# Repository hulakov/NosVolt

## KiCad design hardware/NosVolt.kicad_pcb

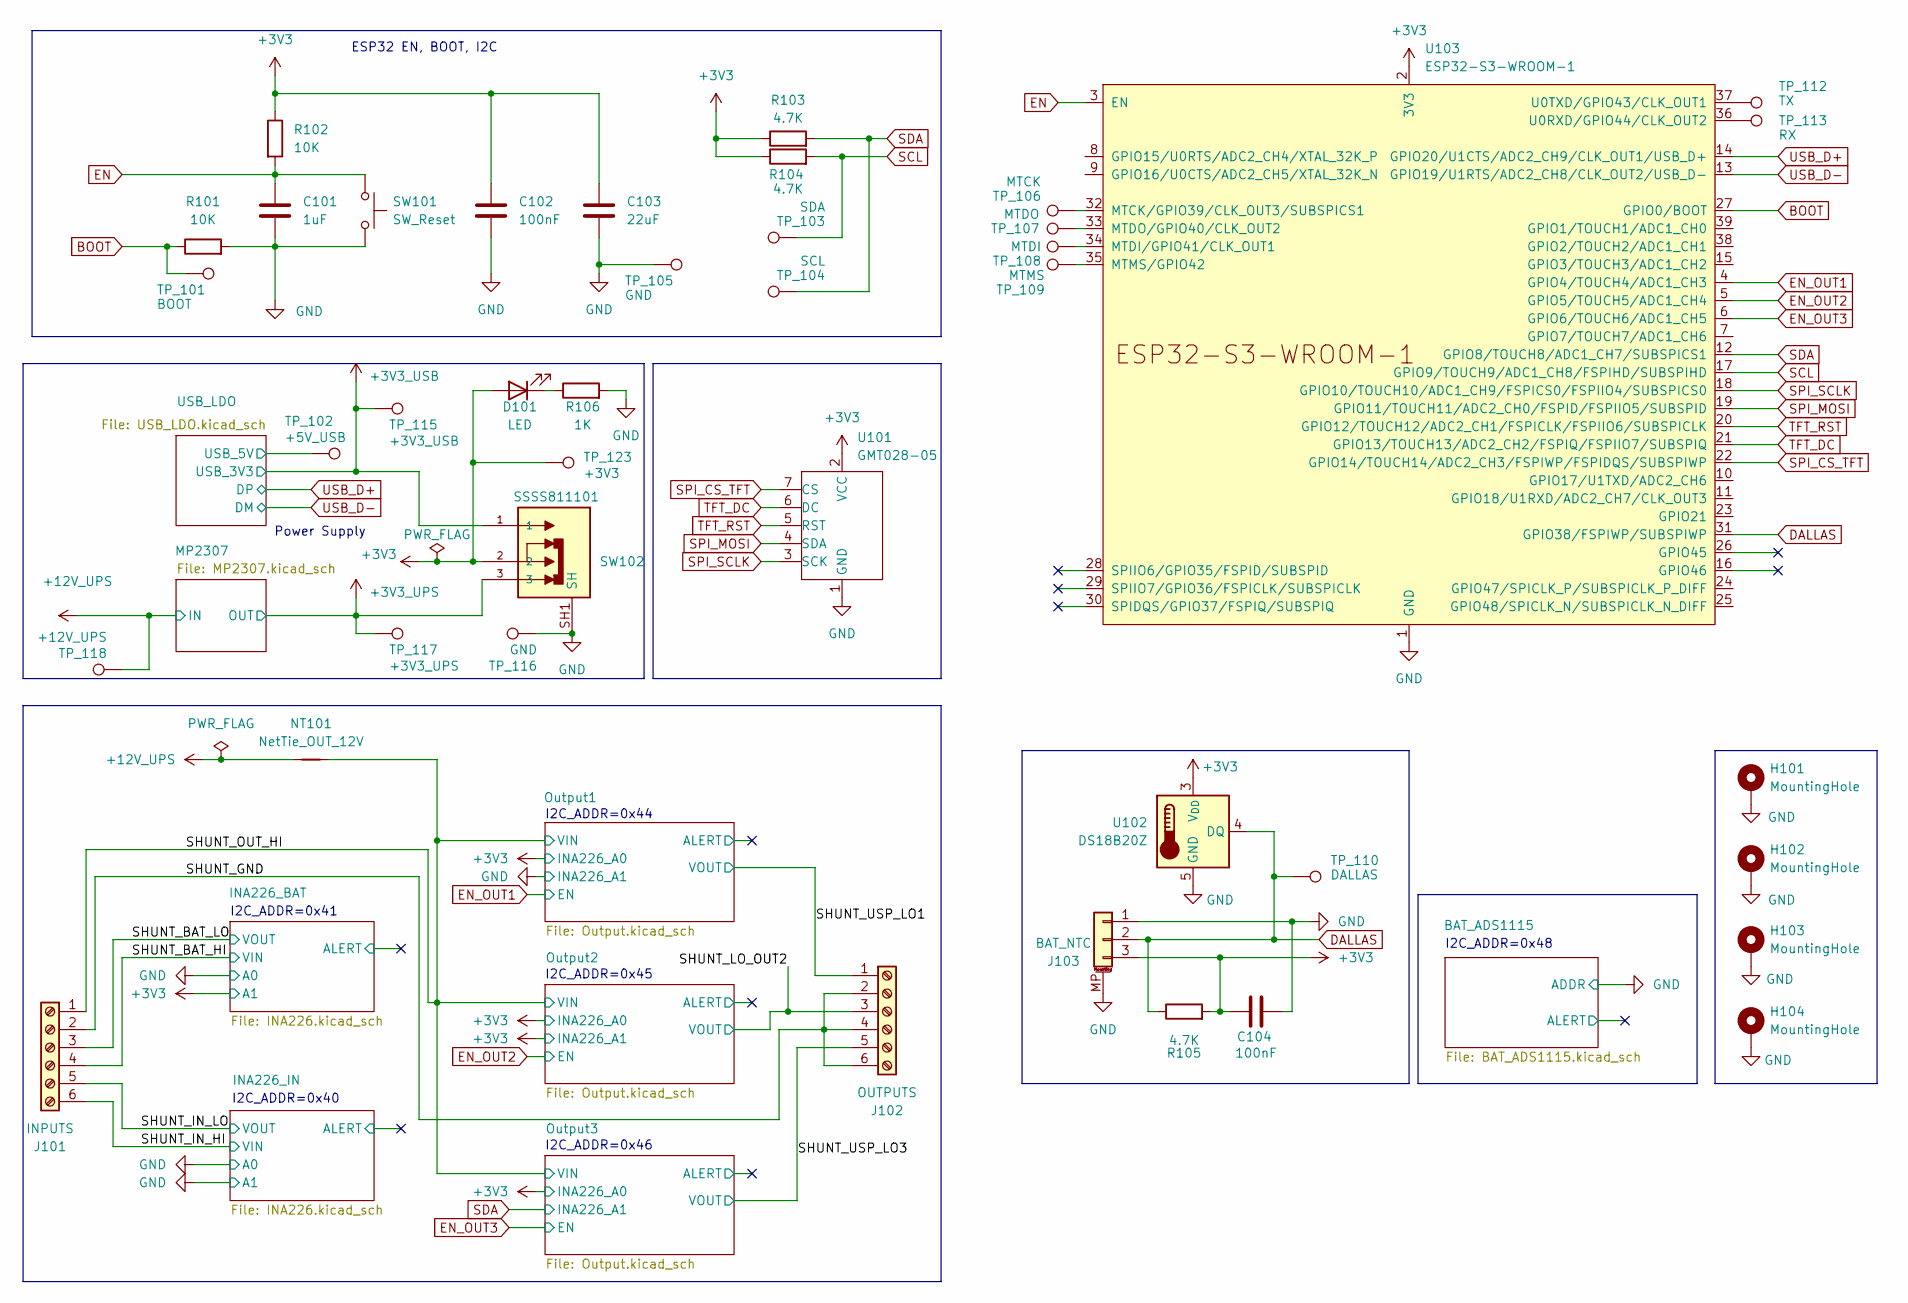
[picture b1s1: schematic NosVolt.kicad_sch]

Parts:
C101: 1uF; C_0805_2012Metric_Pad1.18x1.45mm_HandSolder
C102, C104: 100nF; C_0603_1608Metric_Pad1.08x0.95mm_HandSolder
C103: 22uF; C_0805_2012Metric_Pad1.18x1.45mm_HandSolder
D101: LED; LED_0805_2012Metric_Pad1.15x1.40mm_HandSolder
H101, H102, H103, H104: MountingHole; MountingHole_3.2mm_M3_Pad_Via
J101: INPUTS; TerminalBlock_Phoenix_MKDS-1,5-6-5.08_1x06_P5.08mm_Horizont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
J102: OUTPUTS; TerminalBlock_Phoenix_MKDS-1,5-6-5.08_1x06_P5.08mm_Horizont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
J103: BAT_NTC; JST_GH_SM03B-GHS-TB_1x03-1MP_P1.25mm_Horizontal
NT101: NetTie_OUT_12V; NetTie-2_SMD_Pad0.5mm
R101, R102: 10K; R_0603_1608Metric_Pad0.98x0.95mm_HandSolder
R103, R104, R105: 4.7K; R_0603_1608Metric_Pad0.98x0.95mm_HandSolder
R106: 1K; R_0603_1608Metric_Pad0.98x0.95mm_HandSolder
SW101: SW_Reset; SW_Push_SPST_NO_Alps_SKRK
SW102: SSSS811101; SW_SSSS811101
TP_101: BOOT; TestPoint_Pad_1.0x1.0mm
TP_102: +5V_USB; TestPoint_Pad_1.0x1.0mm
TP_103: SDA; TestPoint_Pad_1.0x1.0mm
TP_104: SCL; TestPoint_Pad_1.0x1.0mm
TP_105, TP_116: GND; TestPoint_Pad_1.0x1.0mm
TP_106: MTCK; TestPoint_Pad_1.0x1.0mm
TP_107: MTDO; TestPoint_Pad_1.0x1.0mm
TP_108: MTDI; TestPoint_Pad_1.0x1.0mm
TP_109: MTMS; TestPoint_Pad_1.0x1.0mm
TP_110: DALLAS; TestPoint_Pad_1.0x1.0mm
TP_112: TX; TestPoint_Pad_1.0x1.0mm
TP_113: RX; TestPoint_Pad_1.0x1.0mm
TP_115: +3V3_USB; TestPoint_Pad_1.0x1.0mm
TP_117: +3V3_UPS; TestPoint_Pad_1.0x1.0mm
TP_118: +12V_UPS; TestPoint_Pad_1.0x1.0mm
TP_123: +3V3; TestPoint_Pad_1.0x1.0mm
U101: GMT028-05
U102: DS18B20Z; SOIC-8_3.9x4.9mm_P1.27mm
U103: ESP32-S3-WROOM-1

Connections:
+3V3: C102.1, C103.1, C104.1, D101.2 (A), J103.3, R102.1, R103.1, R104.1, R105.2, SW102.2, TP_123.1, U101.2 (VCC), U102.3 (V_{DD}), U103.2 (3V3); also elsewhere on the board
+3V3_UPS: SW102.3, TP_117.1; also elsewhere on the board
+3V3_USB: SW102.1, TP_115.1; also elsewhere on the board
+12V_UPS: NT101.1, TP_118.1; also elsewhere on the board
/SHUNT_BAT_HI: J101.4; also elsewhere on the board
/SHUNT_BAT_LO: J101.3; also elsewhere on the board
/SHUNT_GND: J101.2, J102.2, J102.4, J102.6
/SHUNT_IN_HI: J101.6; also elsewhere on the board
/SHUNT_IN_LO: J101.5; also elsewhere on the board
/SHUNT_LO_OUT2: J102.3; also elsewhere on the board
/SHUNT_OUT_HI: J101.1, NT101.2; also elsewhere on the board
/SHUNT_USP_LO1: J102.1; also elsewhere on the board
/SHUNT_USP_LO3: J102.5; also elsewhere on the board
/USB_LDO/USB_5V: TP_102.1; also elsewhere on the board
BOOT: R101.1, TP_101.1, U103.27 (GPIO0/BOOT)
DALLAS: J103.2, R105.1, TP_110.1, U102.4 (DQ), U103.31 (GPIO38/FSPIWP/SUBSPIWP)
EN: C101.1, R102.2, SW101.1, U103.3 (EN)
EN_OUT1: U103.4 (GPIO4/TOUCH4/ADC1_CH3); also elsewhere on the board
EN_OUT2: U103.5 (GPIO5/TOUCH5/ADC1_CH4); also elsewhere on the board
EN_OUT3: U103.6 (GPIO6/TOUCH6/ADC1_CH5); also elsewhere on the board
GND: C101.2, C102.2, C103.2, C104.2, H101.1, H102.1, H103.1, H104.1, J103.1, J103.MP (MountPin), R101.2, R106.2, SW101.2, SW102.SH1 (SH), SW102.SH2 (SH), SW102.SH3 (SH), SW102.SH4 (SH), TP_105.1, TP_116.1, U101.1 (GND), U102.5 (GND), U103.1 (GND), U103.40 (GND), U103.41 (GND); also elsewhere on the board
unnamed: D101.1 (K), R106.1
unnamed: TP_106.1, U103.32 (MTCK/GPIO39/CLK_OUT3/SUBSPICS1)
unnamed: TP_108.1, U103.34 (MTDI/GPIO41/CLK_OUT1)
unnamed: TP_107.1, U103.33 (MTDO/GPIO40/CLK_OUT2)
unnamed: TP_109.1, U103.35 (MTMS/GPIO42)
unnamed: TP_113.1, U103.36 (U0RXD/GPIO44/CLK_OUT2)
unnamed: TP_112.1, U103.37 (U0TXD/GPIO43/CLK_OUT1)
SCL: R104.2, TP_103.1, U103.17 (GPIO9/TOUCH9/ADC1_CH8/FSPIHD/SUBSPIHD); also elsewhere on the board
SDA: R103.2, TP_104.1, U103.12 (GPIO8/TOUCH8/ADC1_CH7/SUBSPICS1); also elsewhere on the board
SPI_CS_TFT: U101.7 (CS), U103.22 (GPIO14/TOUCH14/ADC2_CH3/FSPIWP/FSPIDQS/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)
SPI_MOSI: U101.4 (SDA), U103.19 (GPIO11/TOUCH11/ADC2_CH0/FSPID/FSPIIO5/S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)
SPI_SCLK: U101.3 (SCK), U103.18 (GPIO10/TOUCH10/ADC1_CH9/FSPICS0/FSPIIO4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)
TFT_DC: U101.6 (DC), U103.21 (GPIO13/TOUCH13/ADC2_CH2/FSPIQ/FSPIIO7/S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)
TFT_RST: U101.5 (RST), U103.20 (GPIO12/TOUCH12/ADC2_CH1/FSPICLK/FSPIIO6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)
USB_D+: U103.14 (GPIO20/U1CTS/ADC2_CH9/CLK_OUT1/USB_D+); also elsewhere on the board
USB_D-: U103.13 (GPIO19/U1RTS/ADC2_CH8/CLK_OUT2/USB_D-); also elsewhere on the board

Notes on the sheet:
Power Supply
I2C_ADDR=0x46
I2C_ADDR=0x41
ESP32 EN, BOOT, I2C
I2C_ADDR=0x48
I2C_ADDR=0x45
I2C_ADDR=0x40
I2C_ADDR=0x44

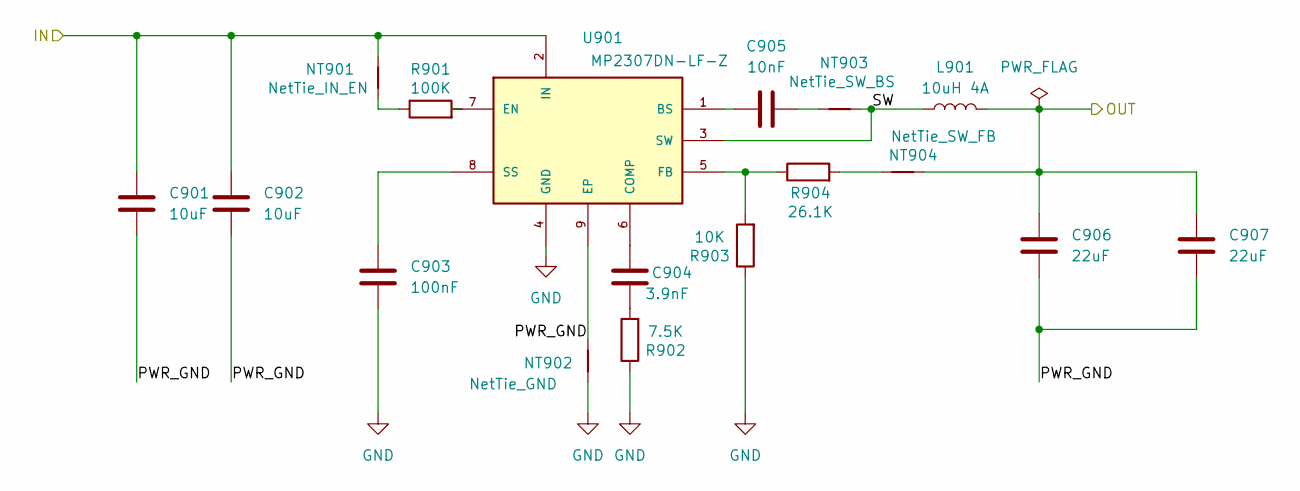
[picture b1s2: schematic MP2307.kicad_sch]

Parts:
C901, C902: 10uF; C_0805_2012Metric_Pad1.18x1.45mm_HandSolder
C903: 100nF; C_0603_1608Metric_Pad1.08x0.95mm_HandSolder
C904: 3.9nF; C_0805_2012Metric_Pad1.18x1.45mm_HandSolder
C905: 10nF; C_0603_1608Metric_Pad1.08x0.95mm_HandSolder
C906, C907: 22uF; C_0805_2012Metric_Pad1.18x1.45mm_HandSolder
L901: 10uH 4A; L_6.3x6.3_H3
NT901: NetTie_IN_EN; NetTie-2_SMD_Pad0.5mm
NT902: NetTie_GND; NetTie-2_SMD_Pad0.5mm
NT903: NetTie_SW_BS; NetTie-2_SMD_Pad0.5mm
NT904: NetTie_SW_FB; NetTie-2_SMD_Pad0.5mm
R901: 100K; R_0603_1608Metric_Pad0.98x0.95mm_HandSolder
R902: 7.5K; R_0603_1608Metric_Pad0.98x0.95mm_HandSolder
R903: 10K; R_0603_1608Metric_Pad0.98x0.95mm_HandSolder
R904: 26.1K; R_0603_1608Metric_Pad0.98x0.95mm_HandSolder
U901: MP2307DN-LF-Z; SOIC-8-1EP_3.9x4.9mm_P1.27mm_EP2.29x3mm_ThermalVias

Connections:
+3V3_UPS: C906.1, C907.1, L901.2, NT904.2; also elsewhere on the board
+12V_UPS: C901.1, C902.1, NT901.1, U901.2 (IN); also elsewhere on the board
/MP2307/PWR_GND: C901.2, C902.2, C906.2, C907.2, NT902.2, U901.9 (EP)
/MP2307/SW: L901.1, NT903.2, U901.3 (SW)
GND: C903.2, NT902.1, R902.1, R903.1, U901.4 (GND); also elsewhere on the board
unnamed: C904.2, R902.2
unnamed: C905.2, NT903.1
unnamed: NT901.2, R901.1
unnamed: NT904.1, R904.2
unnamed: C905.1, U901.1 (BS)
unnamed: C904.1, U901.6 (COMP)
unnamed: R901.2, U901.7 (EN)
unnamed: R903.2, R904.1, U901.5 (FB)
unnamed: C903.1, U901.8 (SS)

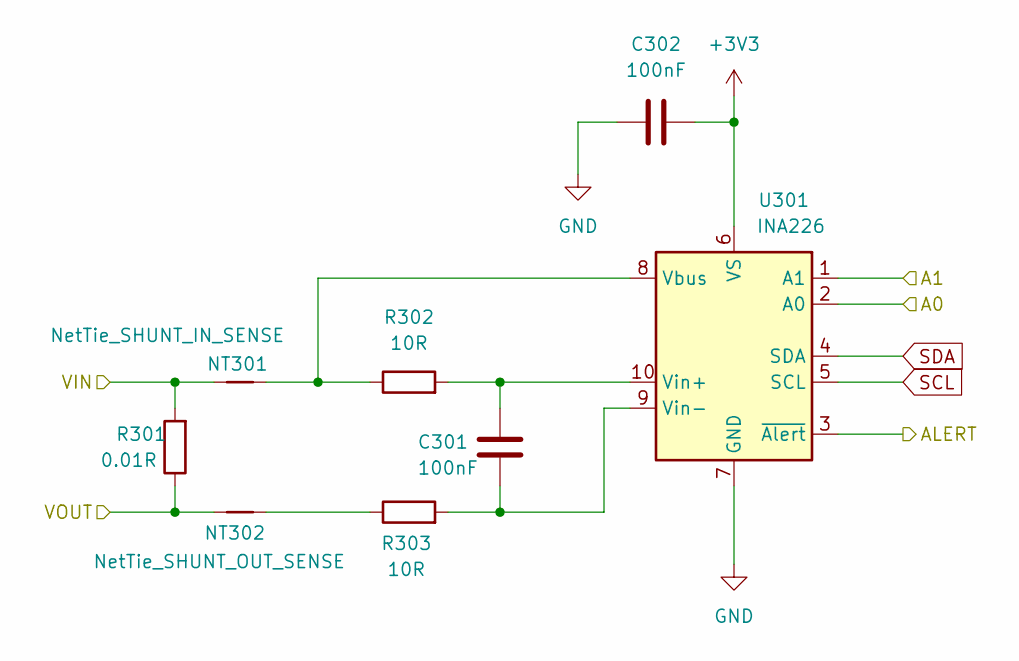
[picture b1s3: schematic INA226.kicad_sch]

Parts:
C301, C302: 100nF; C_0603_1608Metric_Pad1.08x0.95mm_HandSolder
NT301: NetTie_SHUNT_IN_SENSE; NetTie-2_SMD_Pad0.5mm
NT302: NetTie_SHUNT_OUT_SENSE; NetTie-2_SMD_Pad0.5mm
R301: 0.01R; R_2512_6332Metric_Pad1.40x3.35mm_HandSolder
R302, R303: 10R; R_0603_1608Metric_Pad0.98x0.95mm_HandSolder
U301: INA226; VSSOP-10_3x3mm_P0.5mm

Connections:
+3V3: C302.1, U301.6 (VS); also elsewhere on the board
/INA226_IN/ALERT: U301.3 (~Alert)
/SHUNT_IN_HI: NT301.1, R301.2; also elsewhere on the board
/SHUNT_IN_LO: NT302.1, R301.1; also elsewhere on the board
GND: C302.2, U301.1 (A1), U301.2 (A0), U301.7 (GND); also elsewhere on the board
unnamed: NT302.2, R303.1
unnamed: NT301.2, R302.1, U301.8 (Vbus)
unnamed: C301.1, R302.2, U301.10 (Vin+)
unnamed: C301.2, R303.2, U301.9 (Vin-)
SCL: U301.5 (SCL); also elsewhere on the board
SDA: U301.4 (SDA); also elsewhere on the board

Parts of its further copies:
C401, C402, C502, C504, C602, C604, C702, C704: 100nF; C_0603_1608Metric_Pad1.08x0.95mm_HandSolder
NT401, NT502, NT602, NT702: NetTie_SHUNT_IN_SENSE; NetTie-2_SMD_Pad0.5mm
NT402, NT503, NT603, NT703: NetTie_SHUNT_OUT_SENSE; NetTie-2_SMD_Pad0.5mm
R401, R504, R604, R704: 0.01R; R_2512_6332Metric_Pad1.40x3.35mm_HandSolder
R402, R403, R506, R507, R606, R607, R706, R707: 10R; R_0603_1608Metric_Pad0.98x0.95mm_HandSolder
U401, U501, U601, U701: INA226; VSSOP-10_3x3mm_P0.5mm

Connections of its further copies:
+3V3: C402.1, C504.1, C604.1, C704.1, U401.1 (A1), U401.6 (VS), U501.2 (A0), U501.6 (VS), U601.1 (A1), U601.2 (A0), U601.6 (VS), U701.2 (A0), U701.6 (VS); also elsewhere on the board
/INA226_BAT/ALERT: U401.3 (~Alert)
/Output1/ALERT: U701.3 (~Alert)
/Output1/SHUNT_DRAIN: NT702.1, R704.2; also elsewhere on the board
/Output2/ALERT: U601.3 (~Alert)
/Output2/SHUNT_DRAIN: NT602.1, R604.2; also elsewhere on the board
/Output3/ALERT: U501.3 (~Alert)
/Output3/SHUNT_DRAIN: NT502.1, R504.2; also elsewhere on the board
/SHUNT_BAT_HI: NT401.1, R401.2; also elsewhere on the board
/SHUNT_BAT_LO: NT402.1, R401.1; also elsewhere on the board
/SHUNT_LO_OUT2: NT603.1, R604.1; also elsewhere on the board
/SHUNT_USP_LO1: NT703.1, R704.1; also elsewhere on the board
/SHUNT_USP_LO3: NT503.1, R504.1; also elsewhere on the board
GND: C402.2, C504.2, C604.2, C704.2, U401.2 (A0), U401.7 (GND), U501.7 (GND), U601.7 (GND), U701.1 (A1), U701.7 (GND); also elsewhere on the board
unnamed: NT402.2, R403.1
unnamed: NT503.2, R507.1
unnamed: NT603.2, R607.1
unnamed: NT703.2, R707.1
unnamed: NT401.2, R402.1, U401.8 (Vbus)
unnamed: C401.1, R402.2, U401.10 (Vin+)
unnamed: C401.2, R403.2, U401.9 (Vin-)
unnamed: NT502.2, R506.1, U501.8 (Vbus)
unnamed: C502.1, R506.2, U501.10 (Vin+)
unnamed: C502.2, R507.2, U501.9 (Vin-)
unnamed: NT602.2, R606.1, U601.8 (Vbus)
unnamed: C602.1, R606.2, U601.10 (Vin+)
unnamed: C602.2, R607.2, U601.9 (Vin-)
unnamed: NT702.2, R706.1, U701.8 (Vbus)
unnamed: C702.1, R706.2, U701.10 (Vin+)
unnamed: C702.2, R707.2, U701.9 (Vin-)
SCL: U401.5 (SCL), U501.5 (SCL), U601.5 (SCL), U701.5 (SCL); also elsewhere on the board
SDA: U401.4 (SDA), U501.1 (A1), U501.4 (SDA), U601.4 (SDA), U701.4 (SDA); also elsewhere on the board

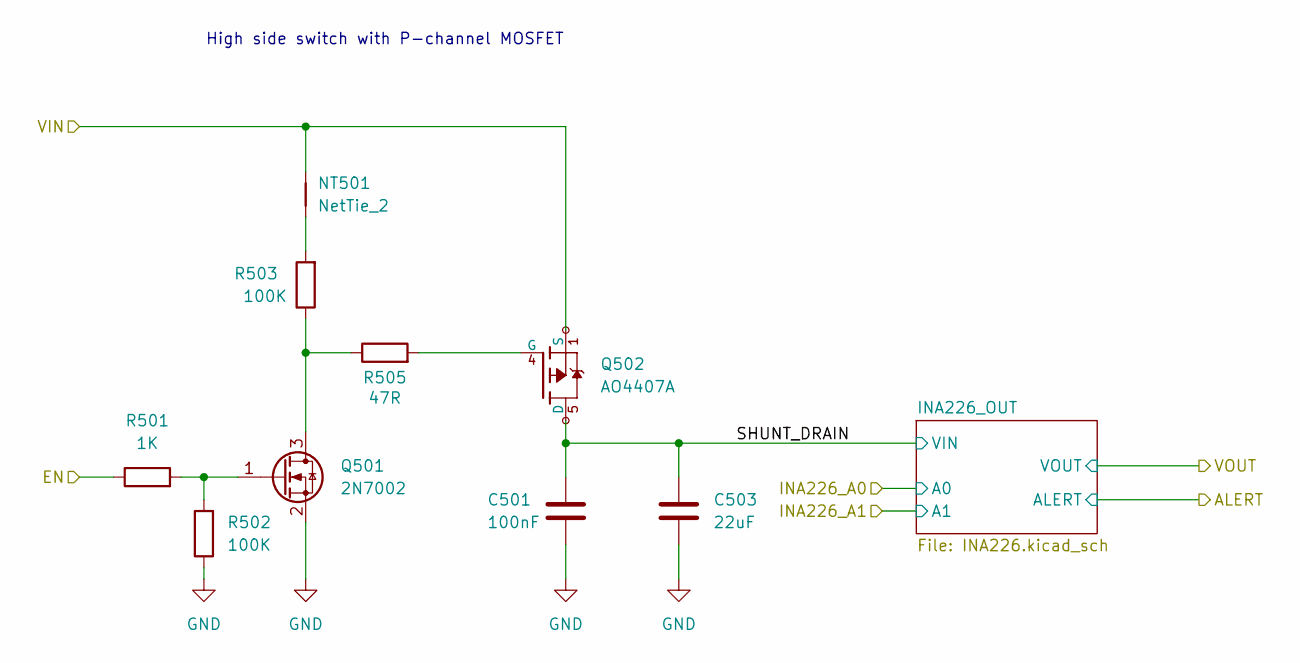
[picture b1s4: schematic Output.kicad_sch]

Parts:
C501: 100nF; C_0603_1608Metric_Pad1.08x0.95mm_HandSolder
C503: 22uF; C_0805_2012Metric_Pad1.18x1.45mm_HandSolder
NT501: NetTie_2; NetTie-2_SMD_Pad0.5mm
Q501: 2N7002; SOT-23
Q502: AO4407A; SOIC-8_3.9x4.9mm_P1.27mm
R501: 1K; R_0603_1608Metric_Pad0.98x0.95mm_HandSolder
R502, R503: 100K; R_0603_1608Metric_Pad0.98x0.95mm_HandSolder
R505: 47R; R_0603_1608Metric_Pad0.98x0.95mm_HandSolder

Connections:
/Output3/SHUNT_DRAIN: C501.1, C503.1, Q502.5 (D), Q502.6 (D), Q502.7 (D), Q502.8 (D); also elsewhere on the board
/SHUNT_OUT_HI: NT501.2, Q502.1 (S), Q502.2 (S), Q502.3 (S); also elsewhere on the board
EN_OUT3: R501.1; also elsewhere on the board
GND: C501.2, C503.2, Q501.2 (S), R502.1; also elsewhere on the board
unnamed: NT501.1, R503.2
unnamed: Q501.3 (D), R503.1, R505.1
unnamed: Q501.1 (G), R501.2, R502.2
unnamed: Q502.4 (G), R505.2

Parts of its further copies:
C601, C701: 100nF; C_0603_1608Metric_Pad1.08x0.95mm_HandSolder
C603, C703: 22uF; C_0805_2012Metric_Pad1.18x1.45mm_HandSolder
NT601, NT701: NetTie_2; NetTie-2_SMD_Pad0.5mm
Q601, Q701: 2N7002; SOT-23
Q602, Q702: AO4407A; SOIC-8_3.9x4.9mm_P1.27mm
R601, R701: 1K; R_0603_1608Metric_Pad0.98x0.95mm_HandSolder
R602, R603, R702, R703: 100K; R_0603_1608Metric_Pad0.98x0.95mm_HandSolder
R605, R705: 47R; R_0603_1608Metric_Pad0.98x0.95mm_HandSolder

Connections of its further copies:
/Output1/SHUNT_DRAIN: C701.1, C703.1, Q702.5 (D), Q702.6 (D), Q702.7 (D), Q702.8 (D); also elsewhere on the board
/Output2/SHUNT_DRAIN: C601.1, C603.1, Q602.5 (D), Q602.6 (D), Q602.7 (D), Q602.8 (D); also elsewhere on the board
/SHUNT_OUT_HI: NT601.2, NT701.2, Q602.1 (S), Q602.2 (S), Q602.3 (S), Q702.1 (S), Q702.2 (S), Q702.3 (S); also elsewhere on the board
EN_OUT1: R701.1; also elsewhere on the board
EN_OUT2: R601.1; also elsewhere on the board
GND: C601.2, C603.2, C701.2, C703.2, Q601.2 (S), Q701.2 (S), R602.1, R702.1; also elsewhere on the board
unnamed: NT601.1, R603.2
unnamed: NT701.1, R703.2
unnamed: Q601.3 (D), R603.1, R605.1
unnamed: Q601.1 (G), R601.2, R602.2
unnamed: Q602.4 (G), R605.2
unnamed: Q701.3 (D), R703.1, R705.1
unnamed: Q701.1 (G), R701.2, R702.2
unnamed: Q702.4 (G), R705.2

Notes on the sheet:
High side switch with P-channel MOSFET

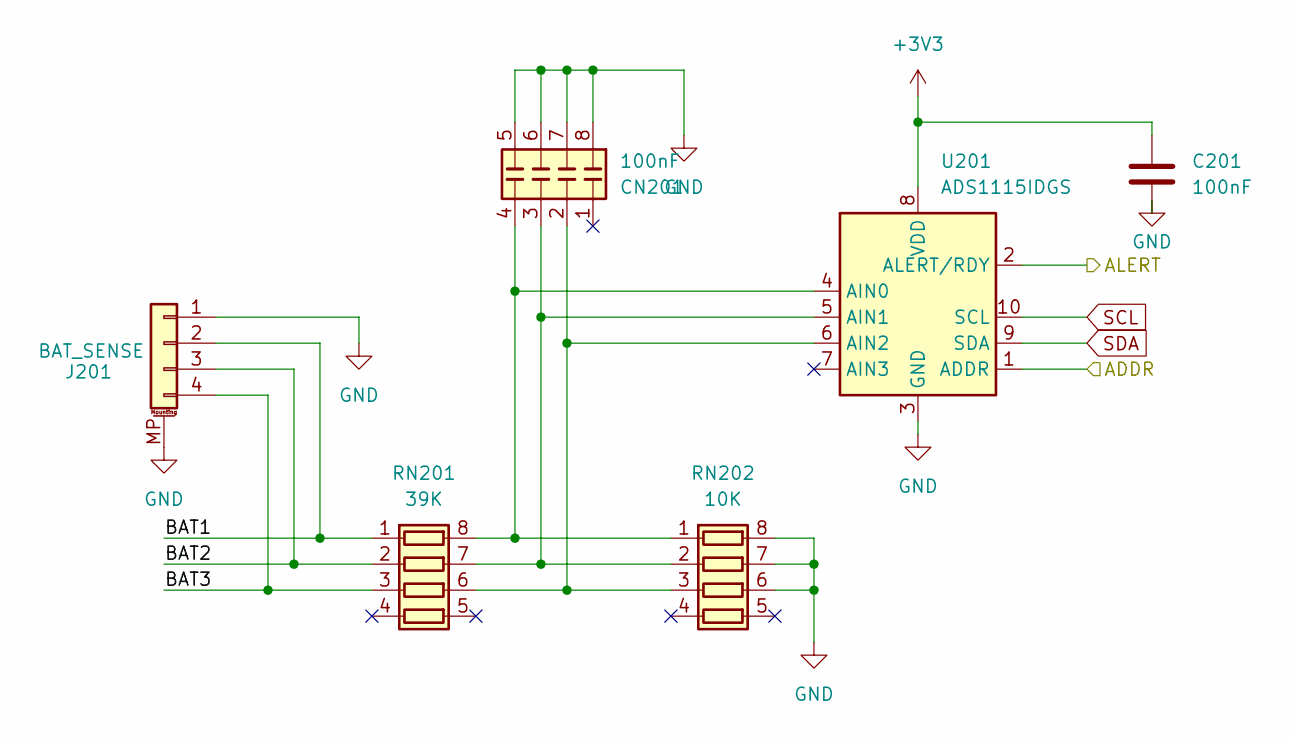
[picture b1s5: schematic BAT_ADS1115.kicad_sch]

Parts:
C201: 100nF; C_0603_1608Metric_Pad1.08x0.95mm_HandSolder
CN201: 100nF; C_Array_Convex_4x0603
J201: BAT_SENSE; JST_GH_SM04B-GHS-TB_1x04-1MP_P1.25mm_Horizontal
RN201: 39K; R_Array_Convex_4x0603
RN202: 10K; R_Array_Convex_4x0603
U201: ADS1115IDGS; TSSOP-10_3x3mm_P0.5mm

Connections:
+3V3: C201.1, U201.8 (VDD); also elsewhere on the board
/BAT_ADS1115/ALERT: U201.2 (ALERT/RDY)
BAT_1: J201.2, RN201.1 (R1.1)
BAT_2: J201.3, RN201.2 (R2.1)
BAT_3: J201.4, RN201.3 (R3.1)
GND: C201.2, CN201.5 (C4.1), CN201.6 (C3.1), CN201.7 (C2.1), CN201.8 (C1.1), J201.1, J201.MP (MountPin), RN202.6 (R3.2), RN202.7 (R2.2), RN202.8 (R1.2), U201.1 (ADDR), U201.3 (GND); also elsewhere on the board
unnamed: CN201.4 (C4.1), RN201.8 (R1.2), RN202.1 (R1.1), U201.4 (AIN0)
unnamed: CN201.3 (C3.1), RN201.7 (R2.2), RN202.2 (R2.1), U201.5 (AIN1)
unnamed: CN201.2 (C2.1), RN201.6 (R3.2), RN202.3 (R3.1), U201.6 (AIN2)
SCL: U201.10 (SCL); also elsewhere on the board
SDA: U201.9 (SDA); also elsewhere on the board

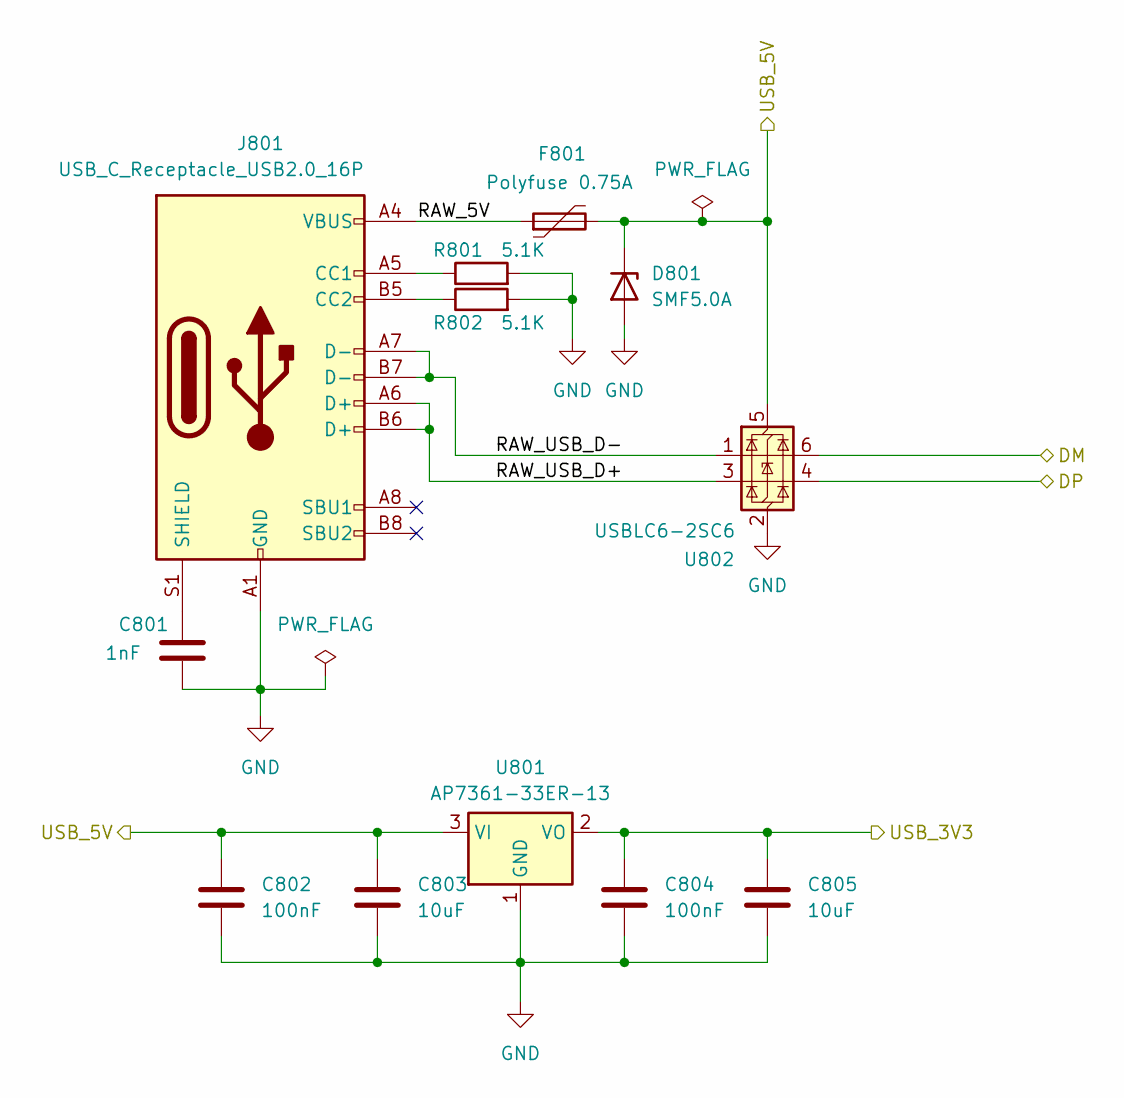
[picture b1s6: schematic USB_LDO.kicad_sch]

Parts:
C801: 1nF; C_0805_2012Metric_Pad1.18x1.45mm_HandSolder
C802, C804: 100nF; C_0603_1608Metric_Pad1.08x0.95mm_HandSolder
C803, C805: 10uF; C_0805_2012Metric_Pad1.18x1.45mm_HandSolder
D801: SMF5.0A; D_SMF
F801: Polyfuse 0.75A; Fuse_0805_2012Metric
J801: USB_C_Receptacle_USB2.0_16P; USB_C_Receptacle_HRO_TYPE-C-31-M-12
R801, R802: 5.1K; R_0603_1608Metric_Pad0.98x0.95mm_HandSolder
U801: AP7361-33ER-13; SOT-223-3_TabPin2
U802: USBLC6-2SC6; SOT-23-6

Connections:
+3V3_USB: C804.1, C805.1, U801.2 (VO); also elsewhere on the board
/USB_LDO/RAW_5V: F801.1, J801.A4 (VBUS), J801.A9 (VBUS), J801.B4 (VBUS), J801.B9 (VBUS)
/USB_LDO/RAW_USB_D+: J801.A6 (D+), J801.B6 (D+), U802.3 (I/O2)
/USB_LDO/RAW_USB_D-: J801.A7 (D-), J801.B7 (D-), U802.1 (I/O1)
/USB_LDO/USB_5V: C802.1, C803.1, D801.1 (K), F801.2, U801.3 (VI), U802.5 (VBUS); also elsewhere on the board
GND: C801.2, C802.2, C803.2, C804.2, C805.2, D801.2 (A), J801.A1 (GND), J801.A12 (GND), J801.B1 (GND), J801.B12 (GND), R801.2, R802.2, U801.1 (GND), U802.2 (GND); also elsewhere on the board
unnamed: J801.A5 (CC1), R801.1
unnamed: J801.B5 (CC2), R802.1
unnamed: C801.1, J801.S1 (SHIELD)
USB_D+: U802.4 (I/O2); also elsewhere on the board
USB_D-: U802.6 (I/O1); also elsewhere on the board

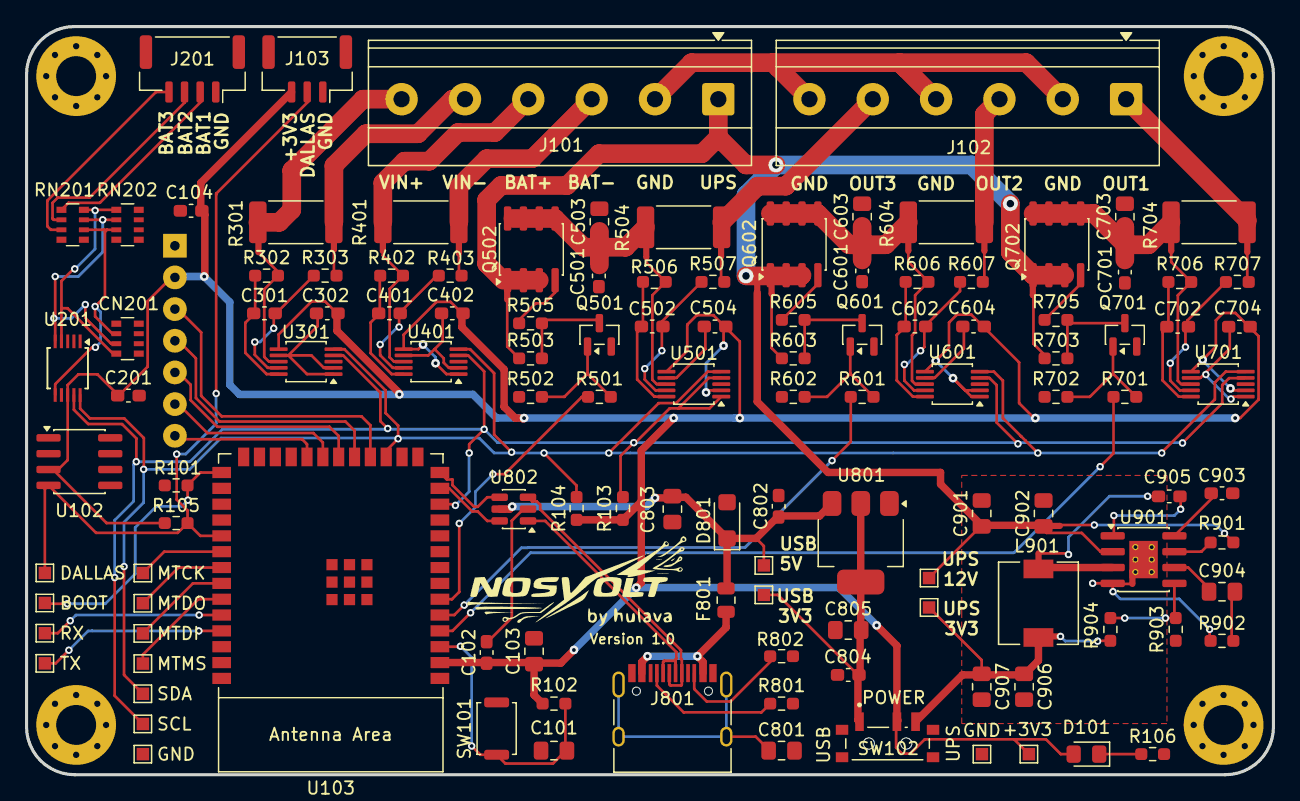
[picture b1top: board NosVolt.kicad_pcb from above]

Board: 2 copper layers, 100.0 x 60.0 mm, 143 parts (1 on the bottom side), 95 nets.

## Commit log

2026-01-01 Outputs and current measurement
2026-01-02 Tracing 1
2026-01-03 Tracing 2
2026-01-04 Tracing 3
2026-01-04 Fixes
2026-01-04 trace ads1115
2026-01-05 ldo optimization
2026-01-05 Add screen
2026-01-06 100*100
2026-01-07 esp32 c3 mini
2026-01-08 thermal relief
2026-01-08 optimization
2026-01-08 tracing
2026-01-08 fix errors
2026-01-08 fix errors 2
2026-01-08 reanotate
2026-01-08 text
2026-01-08 Add logo
2026-01-08 3mm thermal relief
2026-01-10 page numbers
2026-01-11 Test points
2026-01-12 hand soldering footprints and led
2026-01-12 remove fuse
2026-01-12 PWR_FLG
